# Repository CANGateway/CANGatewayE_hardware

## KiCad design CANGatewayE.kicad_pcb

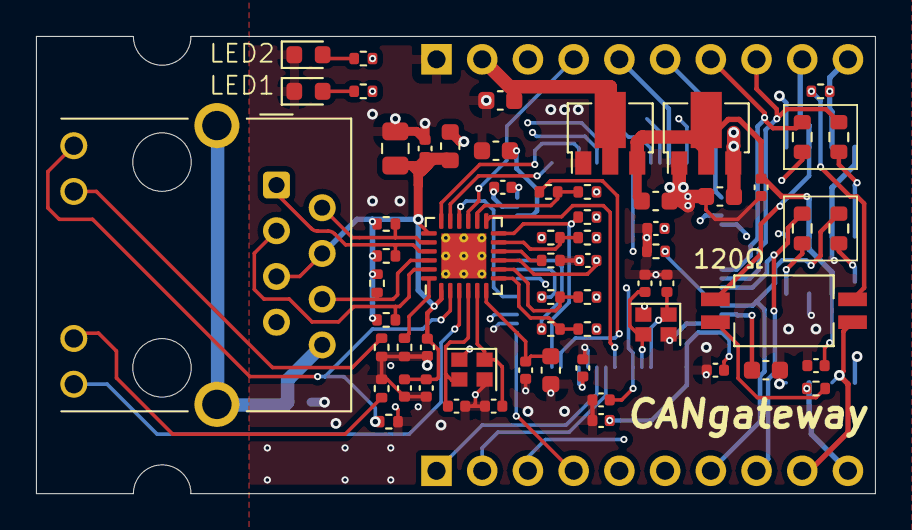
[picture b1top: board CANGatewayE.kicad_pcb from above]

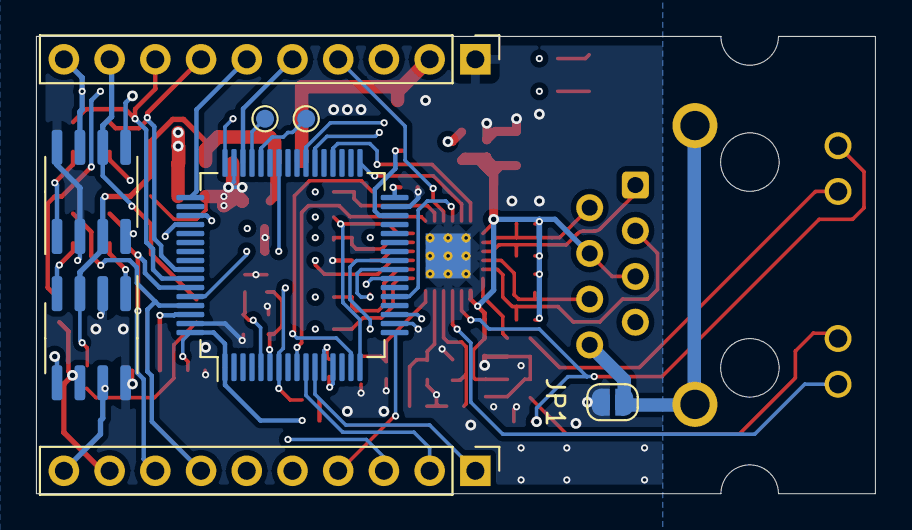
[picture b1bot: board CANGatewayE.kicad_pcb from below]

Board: 4 copper layers, 46.6 x 25.4 mm, 70 parts (8 on the bottom side), 66 nets.

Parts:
C1, C2, C12, C13: 6pF; C_0402_1005Metric
C3, C6, C7, C8, C9, C10, C11, C16, C18, C19, C20, C21, C25: 0.1uF; C_0402_1005Metric
C4, C5: 2.2uF; C_0603_1608Metric
C14: 470pF; C_0402_1005Metric
C15, C24: 1uF; C_0603_1608Metric
C17: 10uF; C_0805_2012Metric
C22, C23: 4.7uF; C_0603_1608Metric
D1, D2: LED; LED_0603_1608Metric
J3, J4: Conn_01x10; PinHeader_1x10_P2.54mm_Vertical
J5: RJ45_Hanrun_HR911105A_Horizontal
JP1: SolderJumper_2_Open; SolderJumper-2_P1.3mm_Open_RoundedPad1.0x1.5mm
JP2, JP3, JP4, JP5: Jumper_2_Bridged; R_0603_1608Metric
L1: 600R@100MHz; L_0603_1608Metric
R1, R23: 10k; R_0402_1005Metric
R2, R3, R4, R5, R6: 10K; R_0402_1005Metric
R7, R8, R9, R10, R11: 33; R_0402_1005Metric
R12, R13, R14, R15: 49.9; R_0402_1005Metric
R16: 12.1k; R_0402_1005Metric
R17, R18: 270; R_0402_1005Metric
R19, R20: 120; R_0402_1005Metric
R21, R22: 2.4k; R_0402_1005Metric
SW1: SW_DIP_x02; SW_DIP_SPSTx02_Slide_Copal_CHS-02B_W7.62mm_P1.27mm
TP1, TP2: TestPoint; TestPoint_Pad_D1.0mm
U1: STM32H563RGTx; LQFP-64_10x10mm_P0.5mm
U2: LAN8742A; VQFN-24-1EP_4x4mm_P0.5mm_EP2.5x2.5mm_ThermalVias
U3, U4: MCP2562FD-E-SN; SOIC-8_3.9x4.9mm_P1.27mm
U5: ME6119A33PG; SOT-89-3
U7: ME6210A50PG; SOT-89-3
Y1: 24MHz; Crystal_SMD_2016-4Pin_2.0x1.6mm
Y2: 25MHz; Crystal_SMD_2016-4Pin_2.0x1.6mm

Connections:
+3.3V: C6.1, C7.1, C8.1, C9.1, C10.1, C16.1, C23.1, J4.3, L1.1, R2.1, R3.1, R4.1, R5.1, R6.1, U1.1 (VBAT), U1.13 (VDDA), U1.19 (VDD), U1.32 (VDD), U1.48 (VDD), U1.64 (VDD), U2.9 (VDDIO), U3.5 (Vio), U4.5 (Vio), U5.3 (VO)
+5V: C11.1, C22.1, C25.1, U3.3 (VDD), U4.3 (VDD), U5.2 (VI), U7.3 (VO)
/CAN1_RD: J3.7, JP3.1 (A), U1.61 (PB8)
/CAN1_TD: J3.8, JP2.1 (A), U1.59 (PB7)
/CAN2_RD: J4.7, JP5.1 (A), U1.57 (PB5)
/CAN2_TD: J4.8, JP4.1 (A), U1.58 (PB6)
/CAN/CAN1_H: J3.10, R19.2, U3.7 (CANH)
/CAN/CAN1_L: J3.9, SW1.3, U3.6 (CANL)
/CAN/CAN2_H: J4.10, R20.1, U4.7 (CANH)
/CAN/CAN2_L: J4.9, SW1.1, U4.6 (CANL)
/Connector/VIN: C24.1, J4.2, U7.2 (VI)
/Ethernet/LED1: J5.12, U2.3 (LED1/REGOFF)
/Ethernet/LED2: J5.9, R23.1, U2.2 (LED2/~INTSEL)
/MCU/BOOT0: R1.1, U1.60 (BOOT0)
/MCU/PA11: TP1.1, U1.44 (PA11)
/MCU/PA12: TP2.1, U1.45 (PA12)
/MCU/PC7: R21.1, U1.38 (PC7)
/MCU/PC8: R22.1, U1.39 (PC8)
/NRST: C3.1, J4.4, U1.7 (NRST), U2.15 (~RST)
/RMII_CRS_DV: R10.1, U1.23 (PA7)
/RMII_MDC: U1.9 (PC1), U2.13 (MDC)
/RMII_MDIO: R5.2, U1.16 (PA2), U2.12 (MDIO)
/RMII_REF_CLK: R11.1, U1.15 (PA1)
/RMII_RXD0: R7.2, U1.24 (PC4)
/RMII_RXD1: R8.2, U1.25 (PC5)
/RMII_TXD0: U1.33 (PB12), U2.17 (TXD0)
/RMII_TXD1: U1.36 (PB15), U2.18 (TXD1)
/RMII_TX_EN: U1.21 (PA5), U2.16 (TXEN)
/SPI3_CS: J3.4, U1.17 (PA3)
/SPI3_MISO: J3.2, U1.10 (PC2)
/SPI3_MOSI: J3.1, U1.11 (PC3)
/SPI3_SCK: J3.3, U1.42 (PA9)
/SWCLK: J4.6, U1.49 (PA14(JTCK)
/SWDIO: J4.5, U1.46 (PA13(JTMS)
/VCP_RX: J3.6, U1.52 (PC11)
/VCP_TX: J3.5, U1.51 (PC10)
GND: C1.2, C2.1, C3.2, C4.2, C5.2, C6.2, C7.2, C8.2, C9.2, C10.2, C11.2, C12.2, C13.1, C14.2, C15.2, C16.2, C17.2, C18.2, C19.2, C20.2, C21.2, C22.2, C23.2, C24.2, C25.2, D1.1 (K), D2.1 (K), J4.1, JP1.2 (B), R1.2, R9.1, R16.2, R17.2, R18.2, R23.2, U1.12 (VSSA), U1.18 (VSS), U1.31 (VSS), U1.47 (VSS), U1.63 (VSS), U2.25 (VSS), U3.2 (VSS), U3.8 (STBY), U4.2 (VSS), U4.8 (STBY), U5.1 (GND), U7.1 (GND), Y1.2, Y1.4, Y2.2, Y2.4
unnamed: C4.1, U1.30 (VCAP)
unnamed: C5.1, U1.62 (VCAP)
unnamed: D1.2 (A), R21.2
unnamed: D2.2 (A), R22.2
unnamed: J5.10, R18.1
unnamed: J5.11, R17.1
unnamed: C17.1, C18.1, C19.1, C20.1, C21.1, J5.4 (TCT), J5.5 (RCT), L1.2, R12.1, R13.1, R14.1, R15.1, U2.1 (VDD2A), U2.19 (VDD1A)
unnamed: J5.3 (RD+), R14.2, U2.23 (RXP)
unnamed: J5.6 (RD-), R15.2, U2.22 (RXN)
unnamed: J5.1 (TD+), R12.2, U2.21 (TXP)
unnamed: J5.2 (TD-), R13.2, U2.20 (TXN)
unnamed: J5.8, J5.SH, JP1.1 (A)
unnamed: JP2.2 (B), U3.1 (TXD)
unnamed: JP3.2 (B), U3.4 (RXD)
unnamed: JP4.2 (B), U4.1 (TXD)
unnamed: JP5.2 (B), U4.4 (RXD)
unnamed: R19.1, SW1.2
unnamed: R20.2, SW1.4
unnamed: C1.1, U1.5 (PH0), Y1.1
unnamed: C2.2, U1.6 (PH1), Y1.3
unnamed: R4.2, R10.2, U2.11 (CRS_DV/MODE2)
unnamed: R16.1, U2.24 (RBIAS)
unnamed: R2.2, R7.1, U2.8 (RXD0/MODE0)
unnamed: R3.2, R8.1, U2.7 (RXD1/MODE1)
unnamed: R9.2, U2.10 (RXER/PHYAD0)
unnamed: C14.1, C15.1, U2.6 (VDDCR)
unnamed: C12.1, U2.5 (XTAL1/CLKIN), Y2.1
unnamed: C13.2, U2.4 (XTAL2), Y2.3
unnamed: R6.2, R11.2, U2.14 (~INT/REFCLKO)

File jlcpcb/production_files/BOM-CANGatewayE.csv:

Comment,Designator,Footprint,LCSC,Quantity
470pF,C14,C_0402_1005Metric,C106207,1
RJ45_Hanrun_HR911105A_Horizontal,J5,RJ45_Hanrun_HR911105A_Horizontal,C12074,1
MCP2562FD-E-SN,"U3,U4",SOIC-8_3.9x4.9mm_P1.27mm,C124016,2
33,"R10,R11,R7,R8,R9",R_0402_1005Metric,C137880,5
270,"R17,R18",R_0402_1005Metric,C137892,2
0.1uF,"C10,C11,C16,C18,C19,C20,C21,C25,C3,C6,C7,C8,C9",C_0402_1005Metric,C1525,13
6pF,"C1,C12,C13,C2",C_0402_1005Metric,C1575,4
1uF,"C15,C24",C_0603_1608Metric,C15849,2
10uF,C17,C_0805_2012Metric,C15850,1
4.7uF,"C22,C23",C_0603_1608Metric,C19666,2
24MHz,Y1,Crystal_SMD_2016-4Pin_2.0x1.6mm,C1985381,1
Jumper_2_Bridged,"JP2,JP3,JP4,JP5",R_0603_1608Metric,C21189,4
2.2uF,"C4,C5",C_0603_1608Metric,C23630,2
120,"R19,R20",R_0402_1005Metric,C25079,2
10k,"R1,R2,R23,R3,R4,R5,R6",R_0402_1005Metric,C25744,7
12.1k,R16,R_0402_1005Metric,C25852,1
2.4k,"R21,R22",R_0402_1005Metric,C25934,2
LED,D1,LED_0603_1608Metric,C2760778,1
600R@100MHz,L1,L_0603_1608Metric,C2971884,1
SW_DIP_x02,SW1,SW_DIP_SPSTx02_Slide_Copal_CHS-02B_W7.62mm_P1.27mm,C40735,1
25MHz,Y2,Crystal_SMD_2016-4Pin_2.0x1.6mm,C5210656,1
LAN8742A,U2,VQFN-24-1EP_4x4mm_P0.5mm_EP2.5x2.5mm_ThermalVias,C621424,1
ME6119A33PG,U5,SOT-89-3,C82566,1
ME6210A50PG,U7,SOT-89-3,C82940,1
49.9,"R12,R13,R14,R15",R_0402_1005Metric,C87044,4
LED,D2,LED_0603_1608Metric,C965809,1
Conn_01x10,J3,PinHeader_1x10_P2.54mm_Vertical,,1
SolderJumper_2_Open,JP1,SolderJumper-2_P1.3mm_Open_RoundedPad1.0x1.5mm,,1
STM32H563RGTx,U1,LQFP-64_10x10mm_P0.5mm,,1
Conn_01x10,J4,PinHeader_1x10_P2.54mm_Vertical,,1
TestPoint,TP2,TestPoint_Pad_D1.0mm,,1
TestPoint,TP1,TestPoint_Pad_D1.0mm,,1

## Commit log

2024-05-22 init
2024-05-22 Create LICENSE
